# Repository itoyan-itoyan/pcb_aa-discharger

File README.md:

# pcb_aa-discharger
4x AA Discharger KiCAD data

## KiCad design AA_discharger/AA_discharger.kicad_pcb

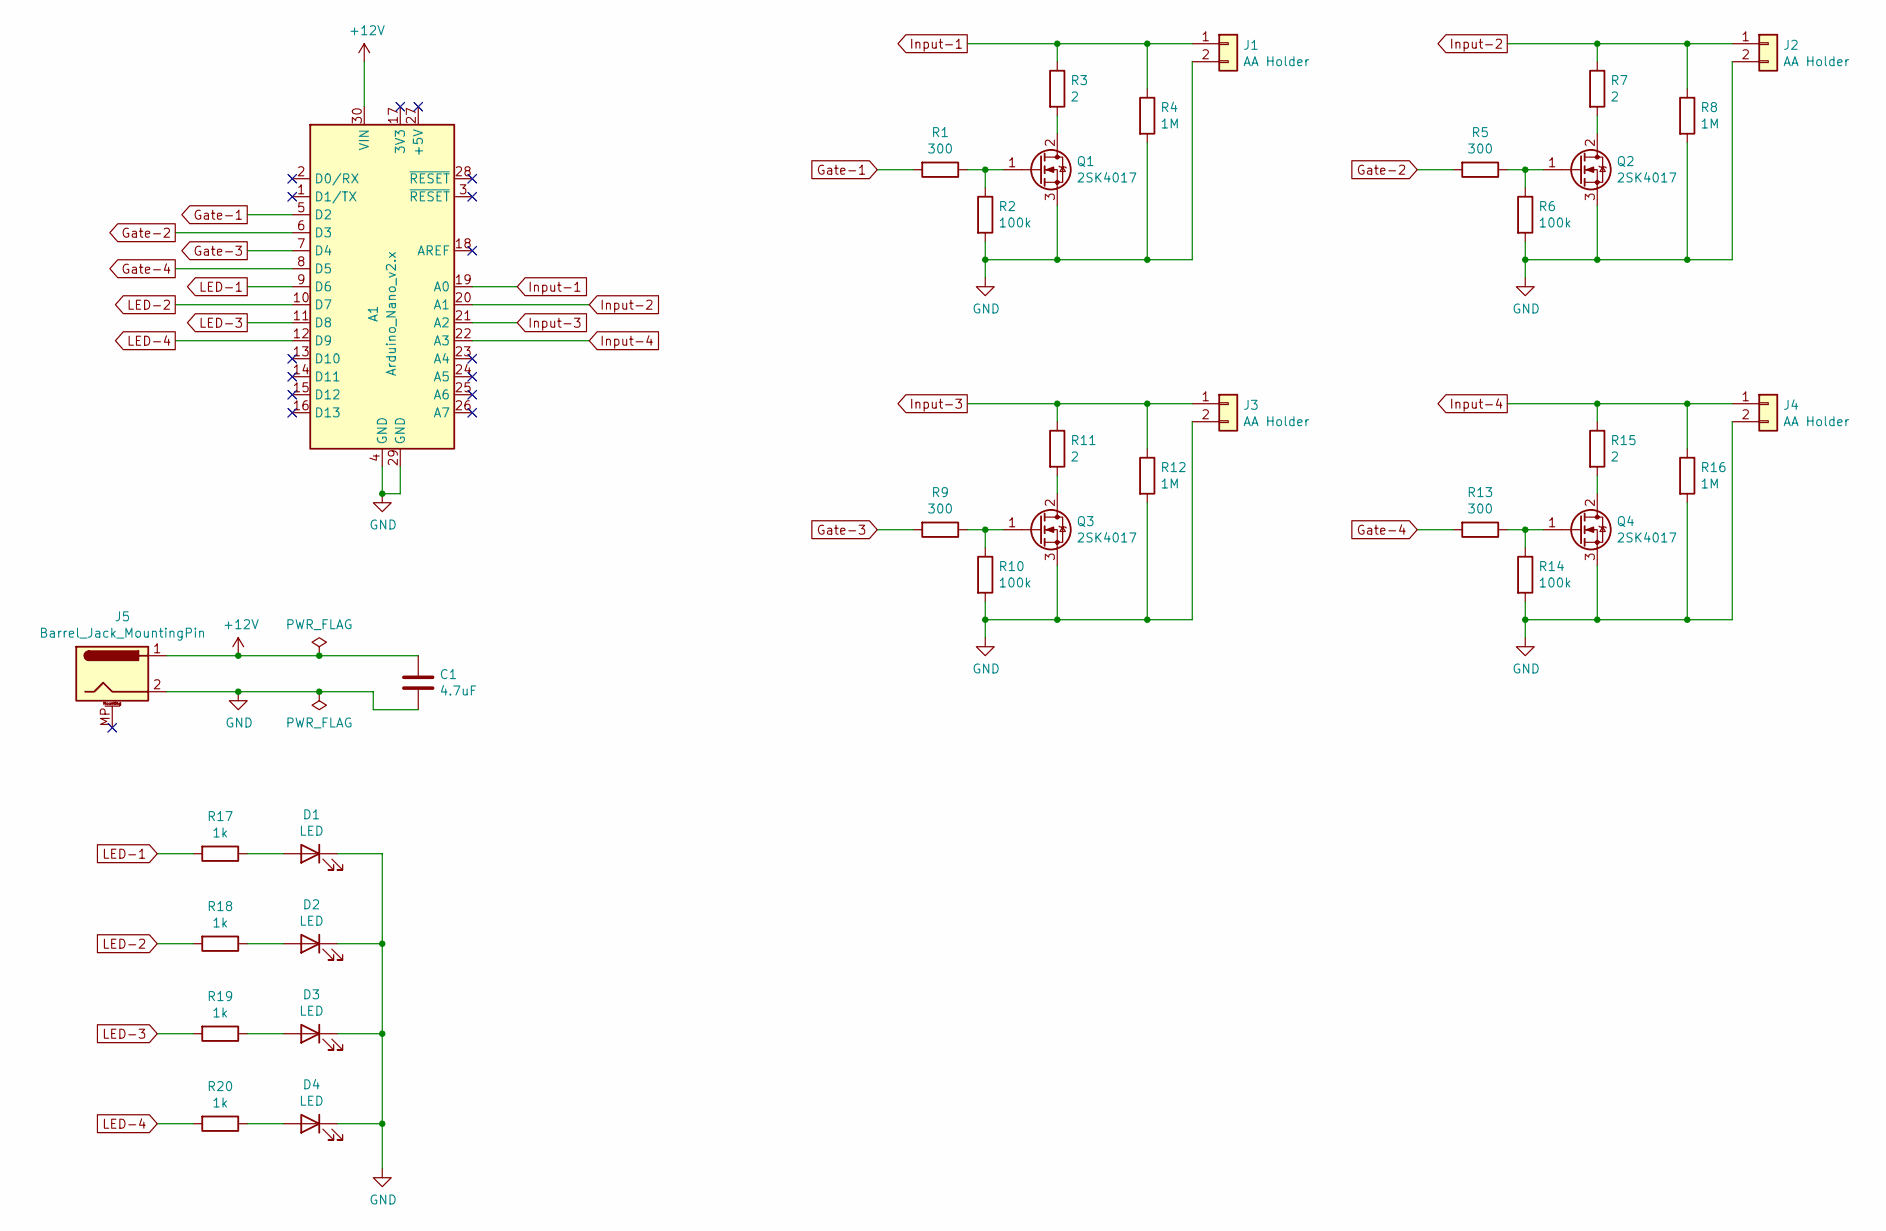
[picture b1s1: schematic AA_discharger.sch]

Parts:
A1: Arduino_Nano_v2.x; Arduino_Nano
C1: 4.7uF; C_1206_3216Metric_Pad1.42x1.75mm_HandSolder
D1, D2, D3, D4: LED; LED_D5.0mm
J1, J2, J3, J4: AA Holder; BatteryHolder_Keystone_2460_1xAA
J5: Barrel_Jack_MountingPin; BarrelJack_Horizontal
Q1, Q2, Q3, Q4: 2SK4017; TO-252-2
R1, R5, R9, R13: 300; R_1206_3216Metric_Pad1.42x1.75mm_HandSolder
R2, R6, R10, R14: 100k; R_1206_3216Metric_Pad1.42x1.75mm_HandSolder
R3, R7, R11, R15: 2; R_Axial_DIN0617_L17.0mm_D6.0mm_P20.32mm_Horizontal
R4, R8, R12, R16: 1M; R_1206_3216Metric_Pad1.42x1.75mm_HandSolder
R17, R18, R19, R20: 1k; R_1206_3216Metric_Pad1.42x1.75mm_HandSolder

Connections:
+12V: A1.30 (VIN), C1.1, J5.1
GND: A1.4 (GND), A1.29 (GND), C1.2, D1.1 (K), D2.1 (K), D3.1 (K), D4.1 (K), J1.2, J2.2, J3.2, J4.2, J5.2, Q1.3 (S), Q2.3 (S), Q3.3 (S), Q4.3 (S), R2.2, R4.2, R6.2, R8.2, R10.2, R12.2, R14.2, R16.2
Gate-1: A1.5 (D2), R1.2
Gate-2: A1.6 (D3), R5.2
Gate-3: A1.7 (D4), R9.2
Gate-4: A1.8 (D5), R13.2
Input-1: A1.19 (A0), J1.1, R3.1, R4.1
Input-2: A1.20 (A1), J2.1, R7.1, R8.1
Input-3: A1.21 (A2), J3.1, R11.1, R12.1
Input-4: A1.22 (A3), J4.1, R15.1, R16.1
LED-1: A1.9 (D6), R17.2
LED-2: A1.10 (D7), R18.2
LED-3: A1.11 (D8), R19.2
LED-4: A1.12 (D9), R20.2
unnamed: D1.2 (A), R17.1
unnamed: D2.2 (A), R18.1
unnamed: D3.2 (A), R19.1
unnamed: D4.2 (A), R20.1
unnamed: Q1.1 (G), R1.1, R2.1
unnamed: Q1.2 (D), R3.2
unnamed: Q2.1 (G), R5.1, R6.1
unnamed: Q2.2 (D), R7.2
unnamed: Q3.1 (G), R9.1, R10.1
unnamed: Q3.2 (D), R11.2
unnamed: Q4.1 (G), R13.1, R14.1
unnamed: Q4.2 (D), R15.2

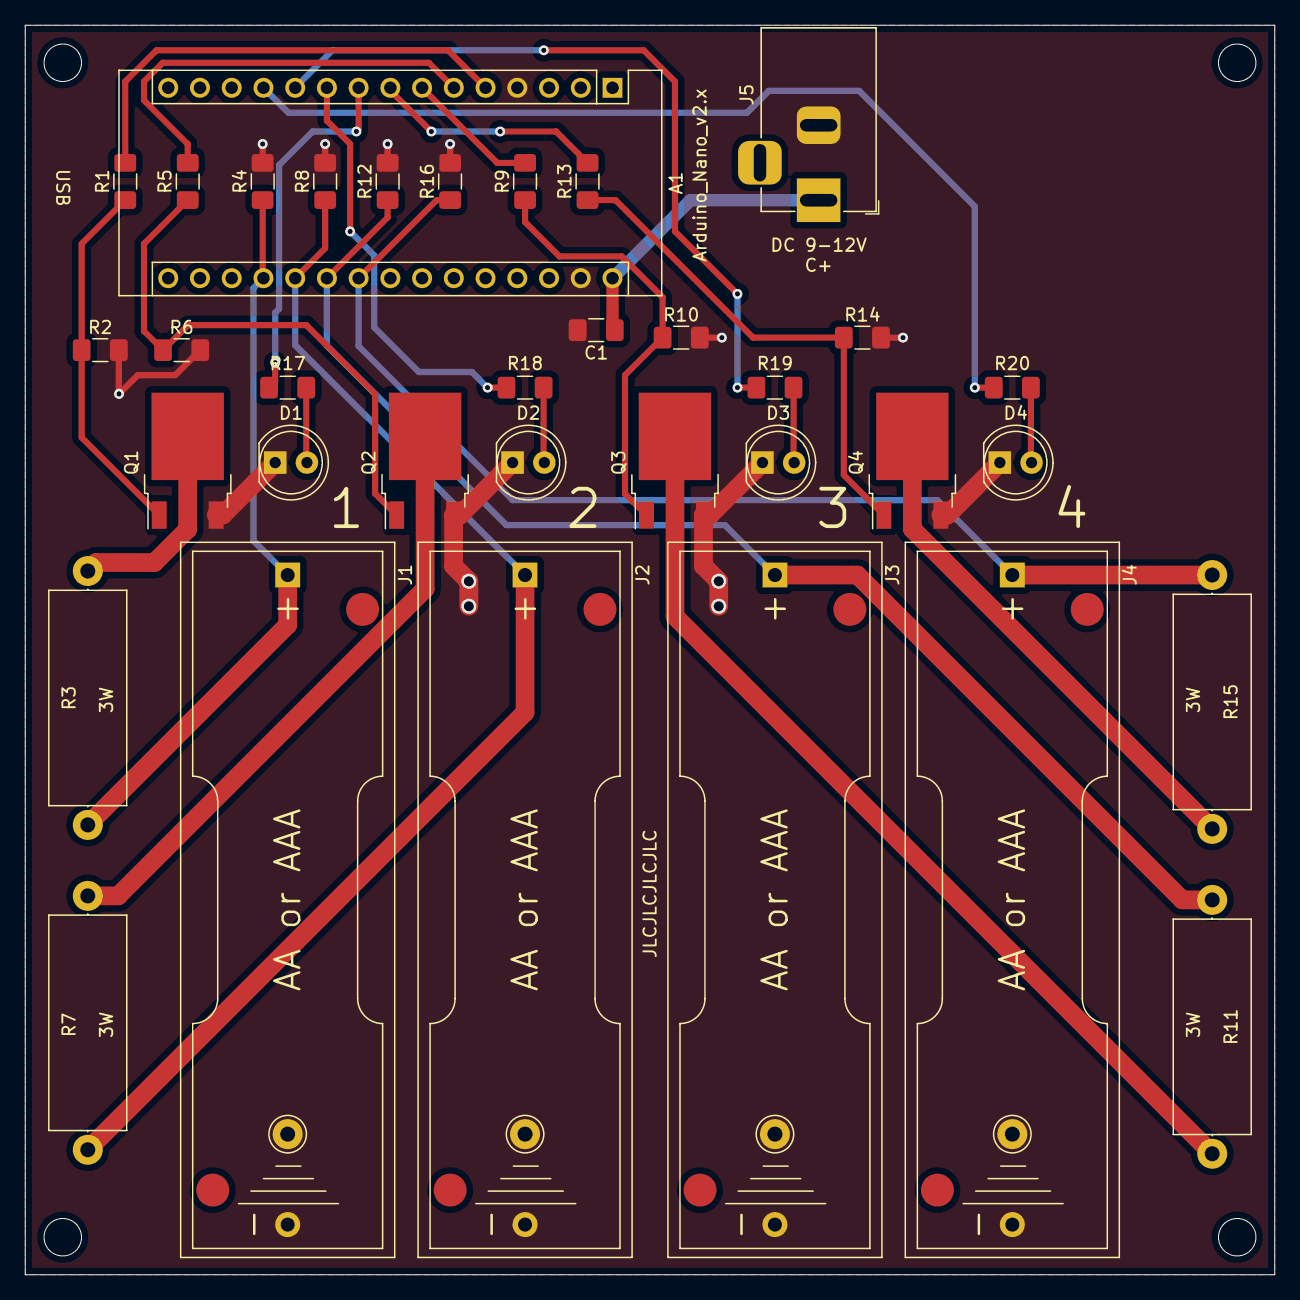
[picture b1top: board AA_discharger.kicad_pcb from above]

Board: 2 copper layers, 100.0 x 100.0 mm, 35 parts (0 on the bottom side), 26 nets.
